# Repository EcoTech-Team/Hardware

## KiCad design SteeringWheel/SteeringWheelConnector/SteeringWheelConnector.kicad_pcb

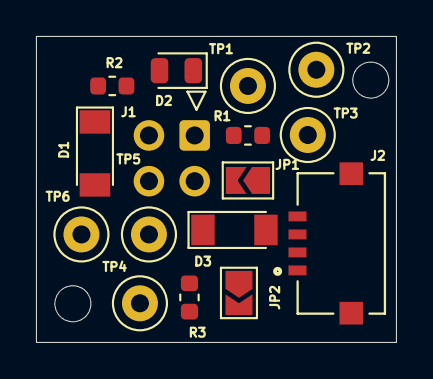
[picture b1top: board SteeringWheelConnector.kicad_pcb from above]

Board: 2 copper layers, 20.0 x 17.0 mm, 19 parts (1 on the bottom side), 7 nets, no tracks yet.

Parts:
D1, D3: D_TVS_ALT; D_MiniMELF
D2: GREEN; LED_0805_2012Metric
G1: EcoTechLogo; EcoTech
H1, H2: MountingHole; MountingHole_3.2mm_M3
J1: Goldpins 2x2; connector2x2
J2: Molex 1x4; MOLEX_5037630491
JP1, JP2: Jumper_NO_Small; SolderJumper-2_P1.3mm_Open_TrianglePad1.0x1.5mm
R1, R3: 120; R_0603_1608Metric
R2: 2k; R_0603_1608Metric
TP1, TP2, TP3, TP4, TP5, TP6: TestPoint; TestPoint_Loop_D1.80mm_Drill1.0mm_Beaded

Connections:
+12V: D1.1, D3.1, J1.3, J2.2, R2.1, TP6.1
/A: J1.2, J2.3, JP1.2, JP2.1, TP3.1, TP5.1
/B: J1.1, J2.4, R1.2, R3.1, TP2.1, TP4.1
GND: D1.2, D2.1, D3.2, J1.4, J2.1, TP1.1
unnamed: D2.2, R2.2
unnamed: JP1.1, R1.1
unnamed: JP2.2, R3.2

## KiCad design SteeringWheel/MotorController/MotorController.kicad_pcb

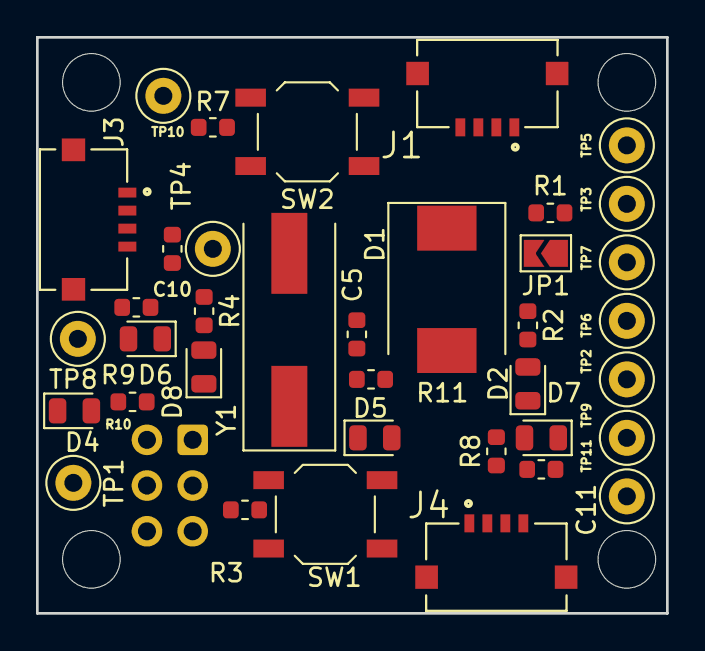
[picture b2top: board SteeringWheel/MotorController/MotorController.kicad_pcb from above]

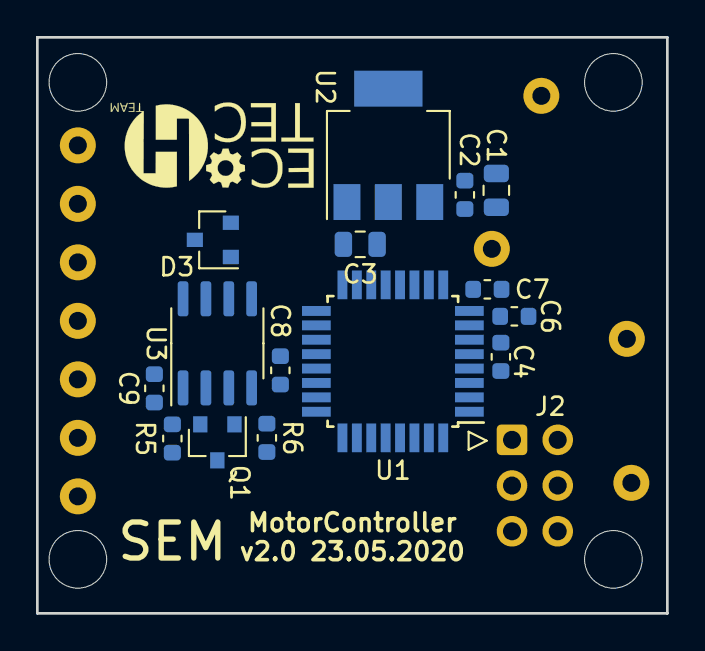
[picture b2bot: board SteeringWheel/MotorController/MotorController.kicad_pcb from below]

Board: 2 copper layers, 35.0 x 32.0 mm, 58 parts (17 on the bottom side), 29 nets, no tracks yet.

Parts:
C1, C3: 10u; C_0805_2012Metric
C2, C4, C5, C8, C9, C10, C11: 100n; C_0603_1608Metric
C6, C7: 22p; C_0603_1608Metric
D1: D_TVS_ALT; D_SMC
D2, D5, D6, D7, D8: GREEN; LED_0805_2012Metric
D3: NUP2105L; SOT-23
D4: RED; LED_0805_2012Metric
G1: EcoTechLogo; EcoTech
H1, H2, H3, H4: MountingHole; MountingHole_3.2mm_M3
J1, J3, J4: Molex 1x4; MOLEX_5037630491
J2: AVR-ISP-10; AVR-ISP-6
JP1: Jumper_NO_Small; SolderJumper-2_P1.3mm_Open_TrianglePad1.0x1.5mm
Q1: Q_NMOS_GSD; SOT-23
R1: 120; R_0603_1608Metric
R2: 2k; R_0603_1608Metric
R3, R5, R6, R7: 10k; R_0603_1608Metric
R4, R8, R9, R10, R11: 1k; R_0603_1608Metric
SW1, SW2: SW_Push; SW_SPST_TL3342
TP1, TP2, TP3, TP4, TP5, TP6, TP7, TP8, TP9, TP10, TP11: TestPoint; TestPoint_Loop_D1.80mm_Drill1.0mm_Beaded
U1: ATmega8A-AU; TQFP-32_7x7mm_P0.8mm
U2: LD1117S50TR_SOT223; SOT-223-3_TabPin2
U3: MAX485E; SOIC-8_3.9x4.9mm_P1.27mm
Y1: 8Mhz; Crystal_SMD_HC49-SD

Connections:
+5V: C3.1, C4.1, C5.1, C9.1, C10.1, C11.1, J2.2, J3.4, J4.4, R3.1, R4.1, R5.1, R7.1, R8.1, R9.1, TP4.1, U1.4, U1.6, U1.18, U2.2, U3.8
+12V: C1.1, C2.1, D1.1, J1.3, R2.1, TP5.1, U2.3
/A: D3.1, J1.2, JP1.2, TP7.1, U3.6
/B: D3.2, J1.1, R1.2, TP6.1, U3.7
/LBTN: J3.2, TP10.1, U1.25
/LED_G: R11.1, U1.9
/LED_R: R10.1, U1.2
/LFR_ADC: J3.3, TP8.1, U1.23
/MISO: J2.1, U1.16
/MOSI: J2.4, U1.15
/PBTN: J4.2, TP11.1, U1.26
/PFR_ADC: J4.3, TP9.1, U1.24
/RST: J2.5, R3.2, SW1.2, U1.29
/RX: U1.30, U3.1
/SCK: J2.3, U1.17
/TX: Q1.1, R6.1, U1.31, U3.4
GND: C1.2, C2.2, C3.2, C4.2, C5.2, C6.2, C7.2, C8.2, C9.2, C10.2, C11.2, D1.2, D2.1, D3.3, D4.1, D5.1, D6.1, D7.1, D8.1, J1.4, J2.6, J3.1, J4.1, Q1.2, R6.2, SW1.1, SW2.2, TP1.1, TP2.1, TP3.1, U1.3, U1.5, U1.21, U2.1, U3.5
unnamed: C6.1, U1.7, Y1.1
unnamed: C7.1, U1.8, Y1.2
unnamed: C8.1, U1.20
unnamed: D2.2, R2.2
unnamed: D4.2, R10.2
unnamed: D5.2, R11.2
unnamed: D6.2, R9.2
unnamed: D7.2, R8.2
unnamed: D8.2, R4.2
unnamed: JP1.1, R1.1
unnamed: Q1.3, R5.2, U3.2, U3.3
unnamed: R7.2, SW2.1, U1.11

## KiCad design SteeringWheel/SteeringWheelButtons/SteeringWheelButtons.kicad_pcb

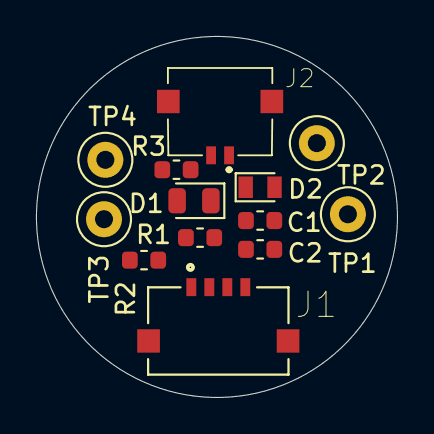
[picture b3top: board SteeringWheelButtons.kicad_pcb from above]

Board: 2 copper layers, 20.1 x 20.1 mm, 18 parts (1 on the bottom side), 5 nets, no tracks yet.

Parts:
C1: 100n; C_0603_1608Metric
C2: 10n; C_0603_1608Metric
D1: GREEN; LED_0805_2012Metric
D2: 30V; D_MicroMELF
G1: EcoTechLogo; EcoTech
H1, H2, H3, H4: MountingHole; MountingHole_3.2mm_M3
J1: Molex 1x4; MOLEX_5037630491
J2: Molex 2x1; 5037630291
R1, R2, R3: 1k; R_0603_1608Metric
TP1, TP2, TP3, TP4: TestPoint; TestPoint_Loop_D1.80mm_Drill1.0mm_Beaded

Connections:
+5V: C1.1, C2.1, D2.1, J1.4, J2.1, R1.1, TP1.1
/BTN: J1.2, J2.2, R3.2, TP4.1
/FR_ADC: J1.3, R2.1, TP3.1
GND: C1.2, C2.2, D1.1, D2.2, J1.1, R2.2, R3.1, TP2.1
unnamed: D1.2, R1.2

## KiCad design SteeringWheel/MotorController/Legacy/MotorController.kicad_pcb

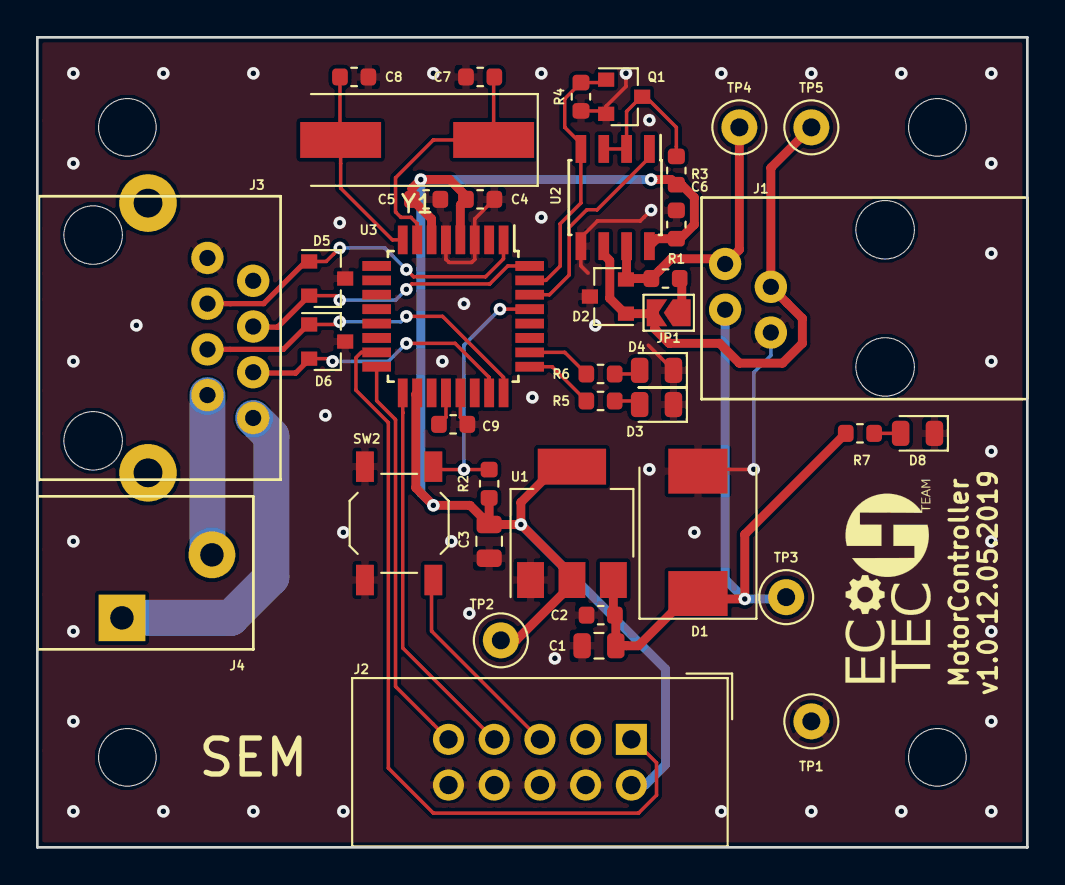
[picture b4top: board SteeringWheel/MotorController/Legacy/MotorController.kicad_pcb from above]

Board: 2 copper layers, 55.0 x 45.0 mm, 44 parts (0 on the bottom side), 27 nets.

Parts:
C1, C3: 10u; C_0805_2012Metric
C2, C4, C5, C6, C9: 100n; C_0603_1608Metric
C7, C8: 22p; C_0603_1608Metric
D1: D_TVS_ALT; D_SMC
D2, D5, D6: NUP2105L; SOT-23
D3: RED; LED_0805_2012Metric
D4, D8: GREEN; LED_0805_2012Metric
G1: EcoTechLogo; EcoTech
H1, H2, H3, H4: MountingHole; MountingHole_3.2mm_M3
J1: 4P4C
J2: AVR-ISP-10; IDC-Header_2x05_P2.54mm_Vertical
J3: 8P8C; MTJ-88GX1-FSD
J4: Screw_Terminal_01x02; TerminalBlock_DG250_02P
JP1: Jumper_NO_Small; SolderJumper-2_P1.3mm_Open_TrianglePad1.0x1.5mm
Q1: Q_NMOS_GSD; SOT-23
R1: 120; R_0603_1608Metric
R2, R3, R4: 10k; R_0603_1608Metric
R5, R6: 1k; R_0603_1608Metric
R7: 2k; R_0603_1608Metric
SW2: SW_Push; SW_SPST_TL3342
TP1, TP2, TP3, TP4, TP5: TestPoint; TestPoint_Loop_D1.80mm_Drill1.0mm_Beaded
U1: LD1117S50TR_SOT223; SOT-223-3_TabPin2
U2: MAX485E; SOIC-8_3.9x4.9mm_P1.27mm
U3: ATmega8A-AU; TQFP-32_7x7mm_P0.8mm
Y1: 8Mhz; Crystal_SMD_HC49-SD

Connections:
+5V: C3.1, C4.1, C5.1, C6.1, J2.2, R2.1, R3.1, TP2.1, U1.2, U2.8, U3.4, U3.6, U3.18
+12V: C1.1, C2.1, D1.1, J1.2, R7.1, TP3.1, U1.3
/A: D2.1, J1.3, JP1.2, TP5.1, U2.6
/B: D2.2, J1.4, R1.2, TP4.1, U2.7
/B1: D5.1, J3.3, U3.1
/B2: D5.2, J3.4, U3.32
/B3: D6.1, J3.5, U3.24
/B4: D6.2, J3.6, U3.23
/BH_N: J3.7, J4.2
/BH_P: J3.8, J4.1
/LED_G: R6.1, U3.26
/LED_R: R5.1, U3.25
/MISO: J2.9, U3.16
/MOSI: J2.1, U3.15
/RST: J2.5, R2.2, SW2.2, U3.29
/RX: U2.1, U3.30
/SCK: J2.7, U3.17
/TX: Q1.1, R4.1, U2.4, U3.31
GND: C1.2, C2.2, C3.2, C4.2, C5.2, C6.2, C7.2, C8.2, C9.2, D1.2, D2.3, D3.1, D4.1, D5.3, D6.3, D8.1, J1.1, J2.4, J2.6, J2.8, J2.10, J3.1, Q1.2, R4.2, SW2.1, TP1.1, U1.1, U2.5, U3.3, U3.5, U3.21
unnamed: C7.1, U3.7, Y1.1
unnamed: C8.1, U3.8, Y1.2
unnamed: C9.1, U3.20
unnamed: D3.2, R5.2
unnamed: D4.2, R6.2
unnamed: D8.2, R7.2
unnamed: JP1.1, R1.1
unnamed: Q1.3, R3.2, U2.2, U2.3

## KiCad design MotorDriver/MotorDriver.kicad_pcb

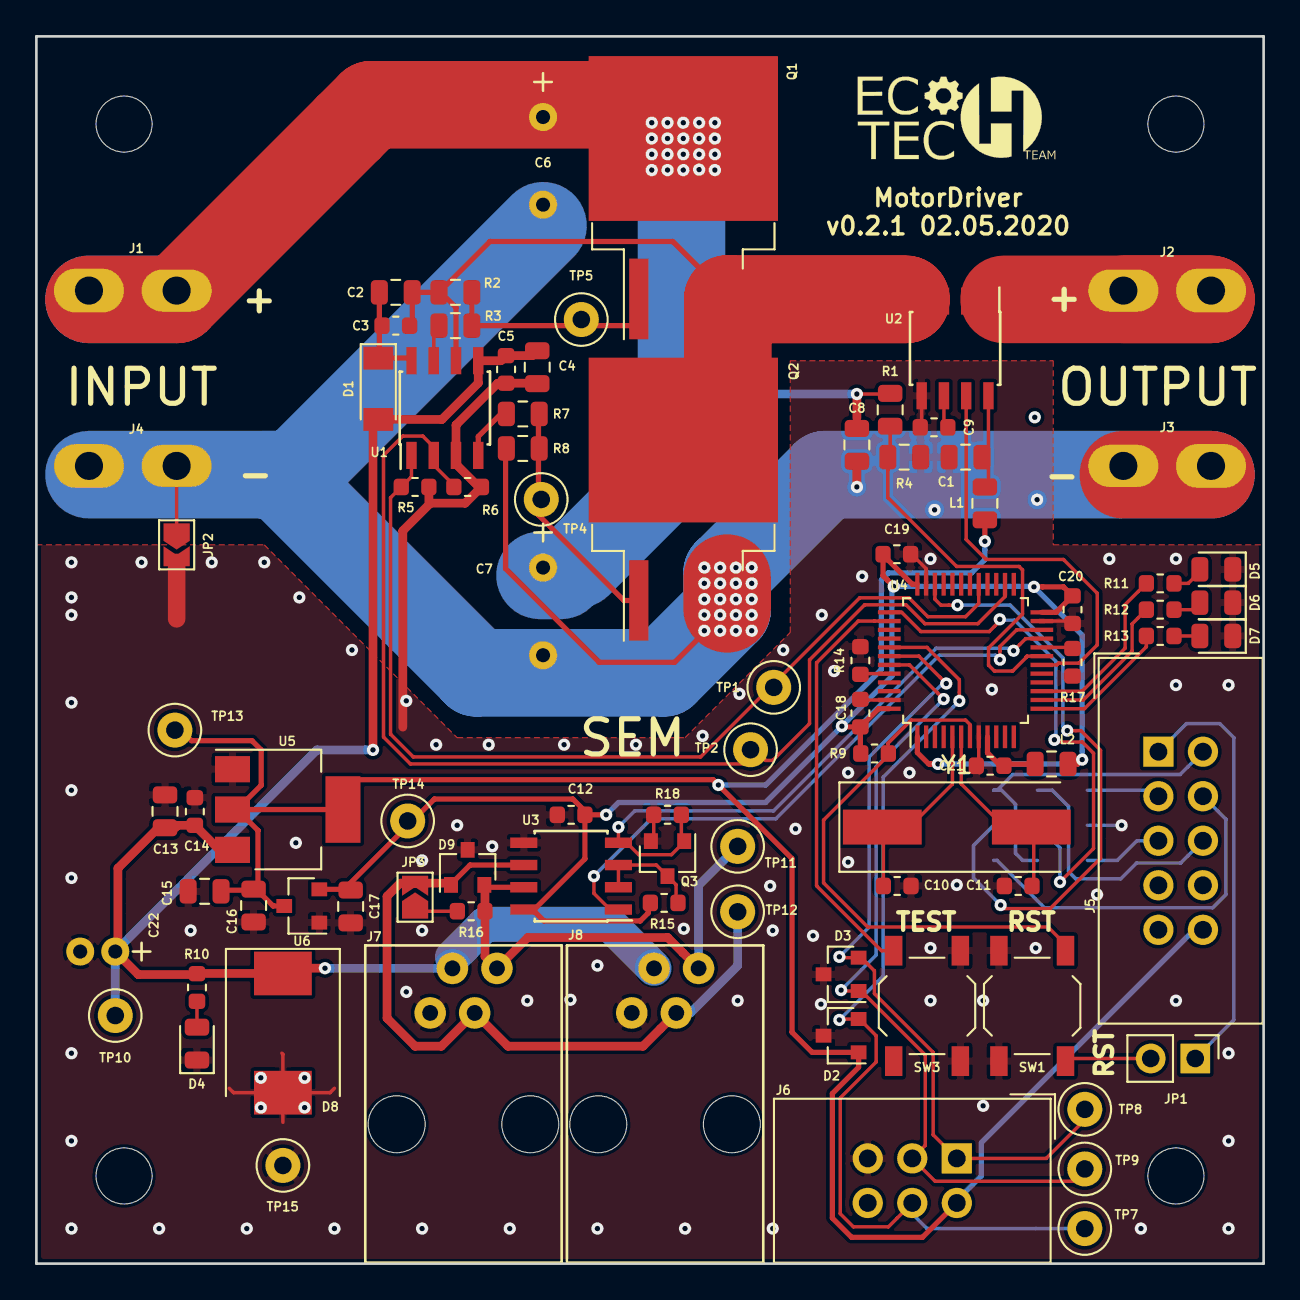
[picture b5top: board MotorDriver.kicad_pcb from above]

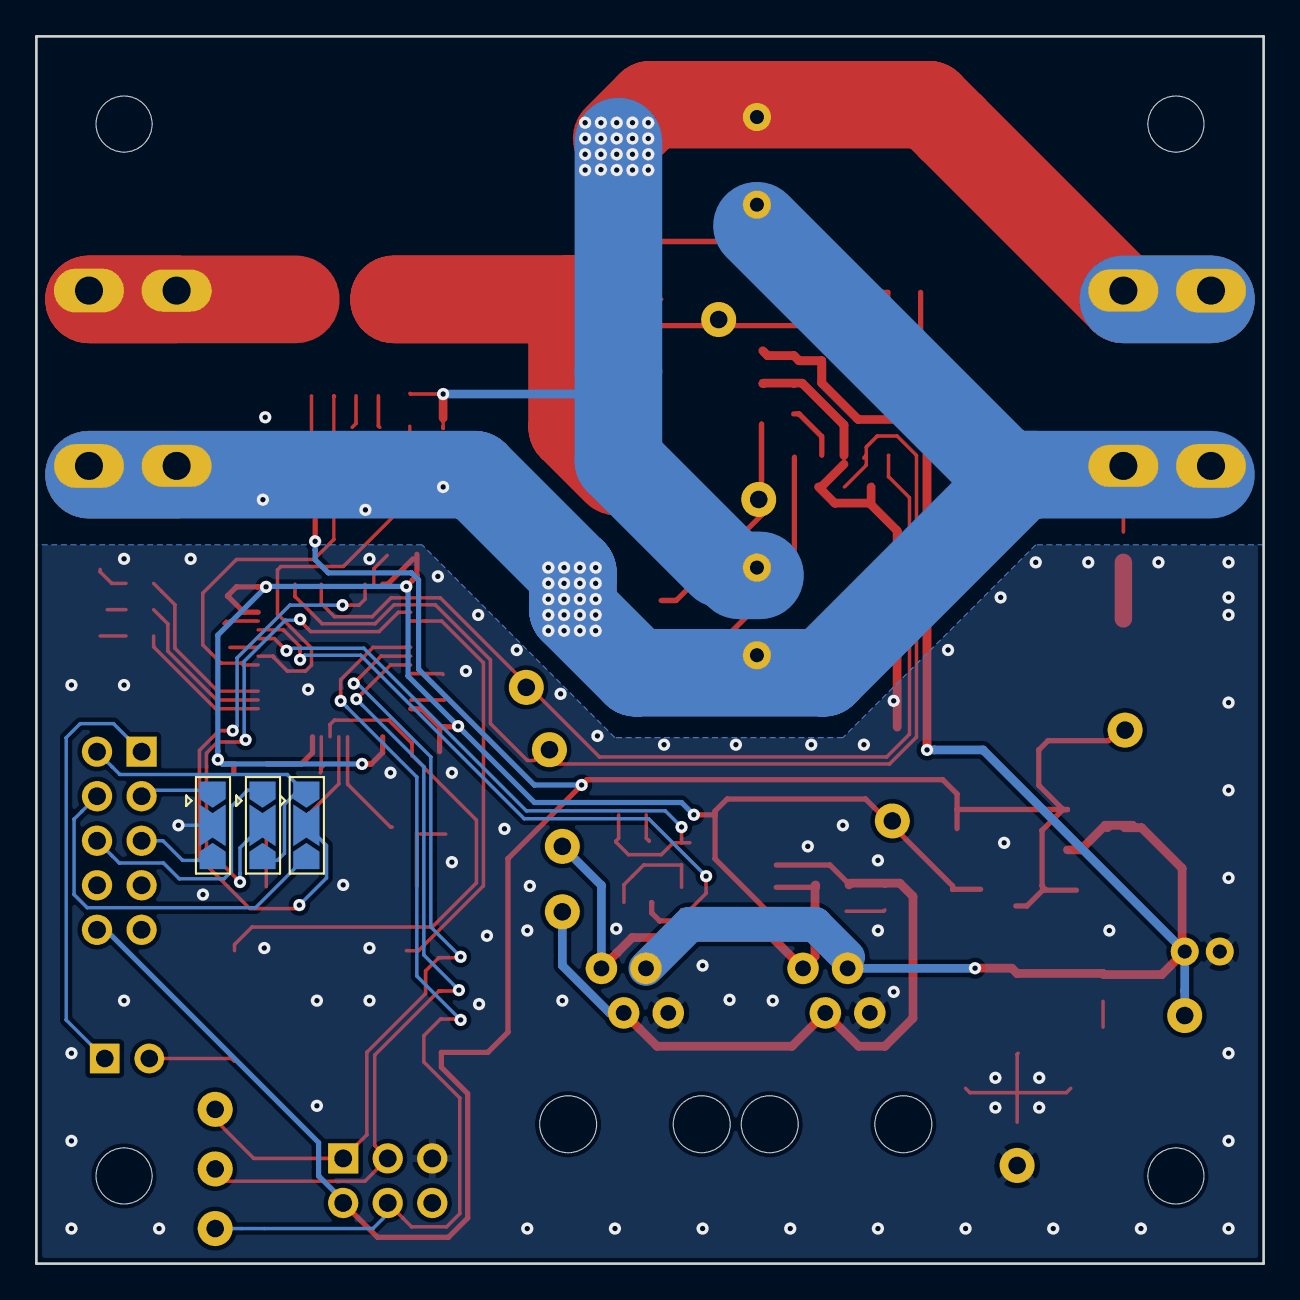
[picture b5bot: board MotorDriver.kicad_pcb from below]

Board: 2 copper layers, 70.0 x 70.0 mm, 95 parts (3 on the bottom side), 50 nets.

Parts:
C1, C8: 100n; C_0805_2012Metric
C2, C4, C13, C15: 10u; C_0805_2012Metric
C3, C5, C12, C14, C18, C19, C20, C21: 100n; C_0603_1608Metric
C6, C7: 680u; C_Radial_D12.5mm_H25.0mm_P5.00mm
C9: 1n; C_0603_1608Metric
C10, C11: 22p; C_0603_1608Metric
C16, C17: 1u; C_0805_2012Metric
C22: 100u; C_Radial_D5.0mm_H11.0mm_P2.00mm
D1: D_ALT; D_MiniMELF
D2, D3, D9: SM712.TCT; SOT-23
D4, D5, D6, D7: GREEN; LED_0805_2012Metric
D8: D_TVS_ALT; D_SMC
G1: EcoTechLogo; EcoTech
H1, H2, H3, H4: MountingHole; MountingHole_3.2mm_M3
J1, J2, J3, J4: Conn_01x01; FlatConnector_63
J5: Conn_02x05_Odd_Even; IDC-Header_2x05_P2.54mm_Vertical
J6: Conn_02x03_Odd_Even; IDC-Header_2x03_P2.54mm_Vertical
J7, J8: 4P4C
JP1: Jumper_NO_Small; PinHeader_1x02_P2.54mm_Vertical
JP2, JP3: Jumper_NO_Small; SolderJumper-2_P1.3mm_Open_TrianglePad1.0x1.5mm
JP4, JP5, JP6: SolderJumper_3_Open; SolderJumper-3_P2.0mm_Open_TrianglePad1.0x1.5mm
L1, L2: 10u; L_0805_2012Metric
Q1, Q2: Q_NMOS_GDS; TO-263-2
Q3: Q_NMOS_GSD; SOT-23
R1: 400k; R_0805_2012Metric
R2, R8: 10k; R_0805_2012Metric
R3, R7: 3R3; R_0805_2012Metric
R4: 35k; R_0805_2012Metric
R5, R6, R9, R10, R15, R18: 10k; R_0603_1608Metric
R11, R12, R13: 1k; R_0603_1608Metric
R14, R17: 100k; R_0603_1608Metric
R16: 120; R_0603_1608Metric
SW1, SW3: SW_Push; SW_SPST_TL3342
TP1, TP2, TP4, TP5, TP7, TP8, TP9, TP10, TP11, TP12, TP13, TP14, TP15: TestPoint; TestPoint_Loop_D1.80mm_Drill1.0mm_Beaded
U1: FAN7190; SOIC-8_3.9x4.9mm_P1.27mm
U2: ACS712xLCTR-20A; SOIC-8_3.9x4.9mm_P1.27mm
U3: MAX485E; SOIC-8_3.9x4.9mm_P1.27mm
U4: STM32F103C8Tx; LQFP-48_7x7mm_P0.5mm
U5: LD1117S50TR_SOT223; SOT-223-3_TabPin2
U6: MCP1700-3302E_SOT23; SOT-23
Y1: 8Mhz; Crystal_SMD_HC49-SD

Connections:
+3.3VA: C21.1, L2.2, U4.9
+3V3: C12.1, C17.1, C18.1, C19.1, C20.1, L2.1, R9.2, R15.1, TP14.1, U3.8, U4.1, U4.24, U4.36, U4.48, U6.2
+5V: C15.1, C16.1, D2.1, J5.10, J6.2, L1.1, TP13.1, U5.2, U6.3
+12V: C4.1, C5.1, C13.1, C14.1, C22.1, D1.2, D8.1, J7.2, J8.2, R10.1, TP10.1, U1.5, U5.3
/2: J5.2, JP4.1, JP6.3
/4: J5.4, JP4.3
/6: J5.6, JP6.1
/A: D9.1, J7.3, J8.3, JP3.2, TP12.1, U3.6
/ADC_I: U2.7, U4.18
/ADC_VIN: R1.2, R4.1, U4.19
/B: D9.2, J7.4, J8.4, R16.1, TP11.1, U3.7
/ENCA: D3.1, J6.3, TP9.1, U4.43
/ENCB: D3.2, J6.1, TP8.1, U4.42
/ENCI: D2.2, J6.4, TP7.1, U4.41
/HG: Q1.1, R2.1, R3.1, TP5.1
/HIN: R5.1, TP1.1, U1.1, U4.29
/LED1: R11.2, U4.15
/LED2: R12.2, U4.14
/LED3: R13.2, U4.13
/LG: Q2.1, R7.1, R8.1, TP4.1
/LIN: R6.1, TP2.1, U1.2, U4.26
/OUT: J2.1, U2.1, U2.2
/RST: JP1.2, R9.1, SW1.2, U4.7
/RX: U3.1, U4.22
/SWCLK: JP6.2, U4.37
/SWDIO: JP4.2, U4.34
/TX: Q3.1, R18.1, U3.4, U4.21
/VS: C2.2, C3.2, Q1.3, Q2.2, R2.2, U1.6, U2.3, U2.4
GND: C1.2, C4.2, C5.2, C9.2, C10.2, C11.2, C12.2, C13.2, C14.2, C15.2, C16.2, C17.2, C18.2, C19.2, C20.2, C21.2, C22.2, D2.3, D3.3, D4.1, D5.1, D6.1, D7.1, D8.2, D9.3, J6.5, J7.1, J8.1, JP2.2, JP5.2, Q3.2, R4.2, R5.2, R6.2, R14.2, R17.2, R18.2, SW1.1, SW3.2, TP15.1, U1.3, U2.5, U3.5, U4.8, U4.23, U4.35, U4.47, U5.1, U6.1
unnamed: C1.1, L1.2, U2.8
unnamed: C2.1, C3.1, D1.1, U1.8
unnamed: C6.1, C7.1, C8.1, J1.1, Q1.2, R1.1
unnamed: C6.2, C7.2, C8.2, J3.1, J4.1, JP2.1, Q2.3, R8.2
unnamed: C9.1, U2.6
unnamed: C10.1, U4.5, Y1.1
unnamed: C11.1, U4.6, Y1.2
unnamed: D4.2, R10.2
unnamed: D5.2, R11.1
unnamed: D6.2, R12.1
unnamed: D7.2, R13.1
unnamed: J5.1, JP1.1
unnamed: J5.3, JP5.1
unnamed: J5.5, JP5.3
unnamed: JP3.1, R16.2
unnamed: Q3.3, R15.2, U3.2, U3.3
unnamed: R3.2, U1.7
unnamed: R7.2, U1.4
unnamed: R14.1, U4.44
unnamed: R17.1, U4.20
unnamed: SW3.1, U4.38

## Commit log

2020-03-22 SteeringWheel/: Create electrical schematics for steering wheel
2020-05-25 SteeringWheel/: Add layouts for motor controller and connector
    Footprints.pretty/: Add molex header, 2x2 connector and AVR
2020-05-25 Library/: Add molex header
    SteeringWheelButtons.sch: Add header footprint
